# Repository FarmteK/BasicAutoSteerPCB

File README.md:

# BasicAutoSteerPCB

Repository of Eagle schematic and board. Parts list spreadsheet that can be imported into DigiKey's BOM and Cart interface. 

The Eagle files are in v7. Gerber and Drill files made by version 9.1.3

Board is roughly 100mm x 127mm or 4x5 inches.

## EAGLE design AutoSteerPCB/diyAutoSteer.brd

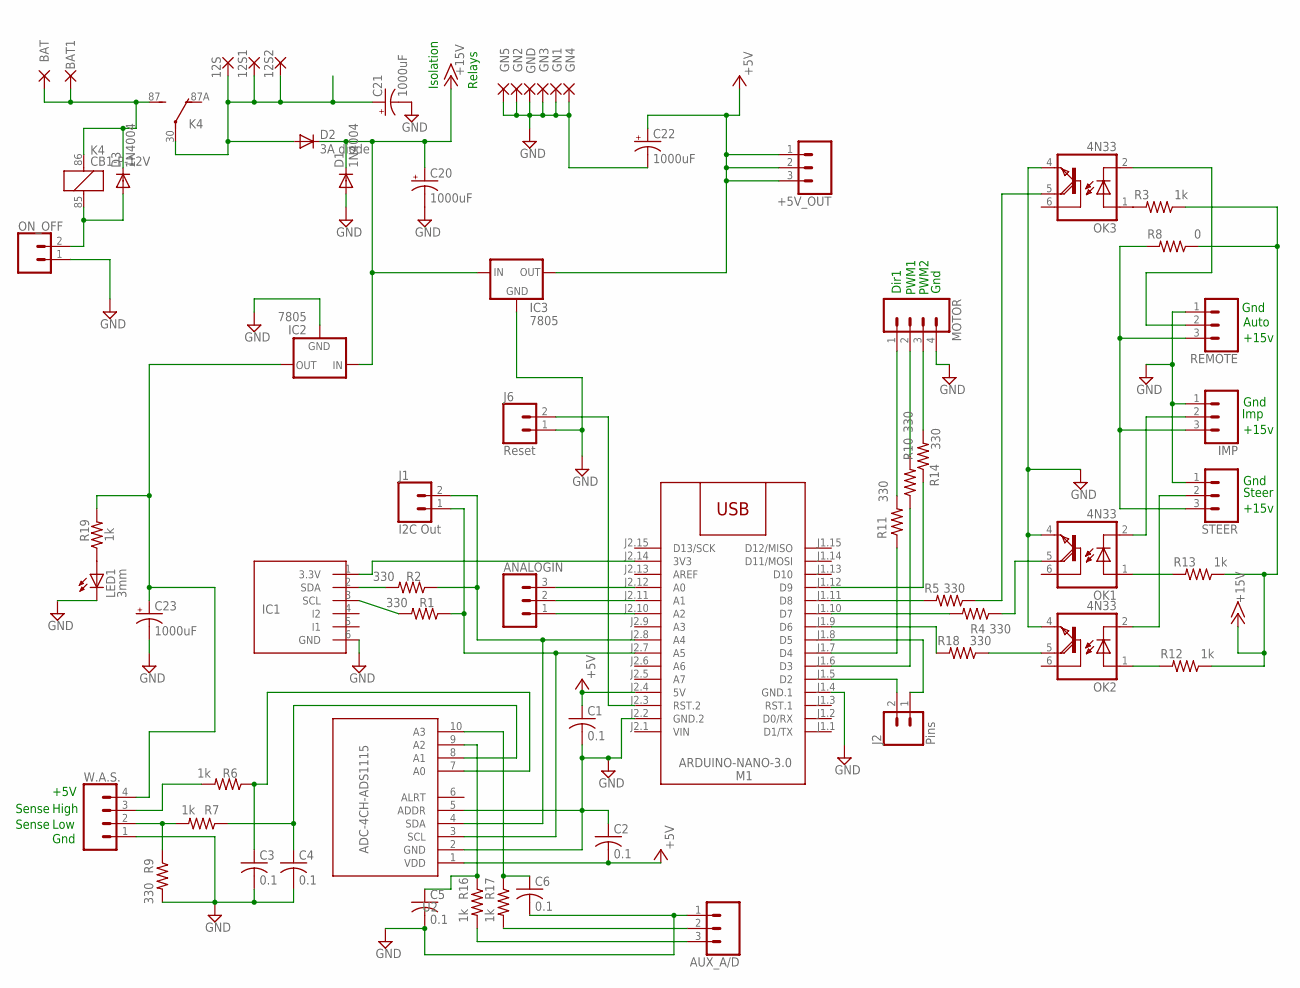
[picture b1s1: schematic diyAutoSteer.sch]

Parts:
12S, 12S1, 12S2: WIREPAD3,81/1,1; 3,81/1,1
+5V_OUT: CONN_03LONGPADS; 1X03_LONGPADS
ANALOGIN: CONN_03LONGPADS; 1X03_LONGPADS
AUX_A/D: CONN_03LONGPADS; 1X03_LONGPADS
BAT, BAT1: WIREPAD3,81/1,1; 3,81/1,1
C1, C2, C3, C4, C5, C6: 0.1; C025-025X050
C20, C21, C22, C23: 1000uF; E5-10,5
D1, D3: 1N4004; DO41-10
D2: 3A diode; DO27-15
GN1, GN2, GN3, GN4, GN5: WIREPAD3,81/1,1; 3,81/1,1
GND: WIREPAD3,81/1,1; 3,81/1,1
IC1: MMA8452Q; BREAKOUT_6PIN
IC2, IC3: 7805; 78XXS
IMP: CONN_03LONGPADS; 1X03_LONGPADS
J1: I2C Out; 1X02_LONGPADS
J2: Pins; 1X02_LONGPADS
J6: Reset; 1X02_LONGPADS
K4: CB1-P-12V; CB1
LED1: 3mm; LED3MM
M1: ARDUINO-NANO-3.0
MOTOR: CONN_04LONGPADS; 1X04_LONGPADS
OK1, OK2, OK3: 4N33; DIL06
ON_OFF: CONN_02PTH3; 1X02_LONGPADS
R1, R2, R4, R5, R9, R10, R11, R14, R18: 330; 0309/12
R3, R6, R7, R12, R13, R16, R17, R19: 1k; 0309/12
R8: 0; 0309/12
REMOTE: CONN_03LONGPADS; 1X03_LONGPADS
STEER: CONN_03LONGPADS; 1X03_LONGPADS
U2: ADC-4CH-ADS1115
W.A.S.: CONN_04LONGPADS; 1X04_LONGPADS

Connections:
+5V: +5V_OUT.1, +5V_OUT.2, +5V_OUT.3, C1.1, C2.2, C22.+, IC3.OUT, M1.J2.4 (5V), U2.1 (VDD)
+15V: C20.+, D1.C, D2.C, IC2.IN, IC3.IN, R3.1, R8.1, R12.1, R13.1
BATT: BAT.1, BAT1.1, D3.C, K4.86 (1), K4.87 (S)
GND: AUX_A/D.1, C1.2, C2.1, C3.2, C4.2, C5.2, C6.2, C20.-, C21.-, C22.-, C23.-, D1.A, GN1.1, GN2.1, GN3.1, GN4.1, GN5.1, GND.1, IC1.6 (GND), IC2.GND, IC3.GND, IMP.1, J6.1, LED1.K (C), M1.J1.4 (GND.1), M1.J2.2 (GND.2), MOTOR.4, OK1.4 (E), OK2.4 (E), OK3.4 (E), ON_OFF.1, R9.2, REMOTE.1, STEER.1, U2.2 (GND), U2.5 (ADDR), W.A.S..1
unnamed: IC1.1 (3.3V), M1.J2.14 (3V3)
unnamed: R7.2, R9.1, W.A.S..2
unnamed: IMP.3, R8.2, REMOTE.3, STEER.3
unnamed: M1.J1.6 (D3), R10.1
unnamed: M1.J1.7 (D4), R11.1
unnamed: J2.2, M1.J1.5 (D2)
unnamed: J6.2, M1.J2.3 (RST.2)
unnamed: R6.2, W.A.S..3
unnamed: ANALOGIN.3, M1.J2.12 (A0)
unnamed: M1.J1.12 (D9), R14.1
unnamed: IC1.2 (SDA), R2.2
unnamed: IC1.3 (SCL), R1.2
unnamed: ANALOGIN.2, M1.J2.11 (A1)
unnamed: ANALOGIN.1, M1.J2.10 (A2)
unnamed: LED1.A, R19.1
unnamed: MOTOR.2, R10.2
unnamed: J2.1, M1.J1.8 (D5)
unnamed: MOTOR.1, R11.2
unnamed: C3.1, R6.1, U2.7 (A0)
unnamed: MOTOR.3, R14.2
unnamed: OK2.2 (C), STEER.2
unnamed: M1.J1.11 (D8), R5.2
unnamed: D3.A, K4.85 (2), ON_OFF.2
unnamed: OK2.1 (A), R12.2
unnamed: OK3.1 (A), R3.2
unnamed: M1.J1.10 (D7), R4.2
unnamed: OK3.2 (C), REMOTE.2
unnamed: IMP.2, OK1.2 (C)
unnamed: M1.J1.9 (D6), R18.2
unnamed: OK1.1 (A), R13.2
unnamed: OK3.5 (COL), R5.1
unnamed: C6.1, R17.1, U2.10 (A3)
unnamed: C5.1, R16.1, U2.9 (A2)
unnamed: OK1.5 (COL), R4.1
unnamed: AUX_A/D.2, R17.2
unnamed: OK2.5 (COL), R18.1
unnamed: C4.1, R7.1, U2.8 (A1)
unnamed: AUX_A/D.3, R16.2
SCL: J1.1, M1.J2.7 (A5), R1.1, U2.3 (SCL)
SDA: J1.2, M1.J2.8 (A4), R2.1, U2.4 (SDA)
SW_RAW: 12S.1, 12S1.1, 12S2.1, C21.+, D2.A, K4.30
V+WAS: C23.+, IC2.OUT, R19.2, W.A.S..4
VIN: M1.J2.1 (VIN)

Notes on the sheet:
Gnd
Low
High
+5V
PWM1
PWM2
Dir1
Steer
Imp
Sense
Auto
Isolation
Relays
+15v

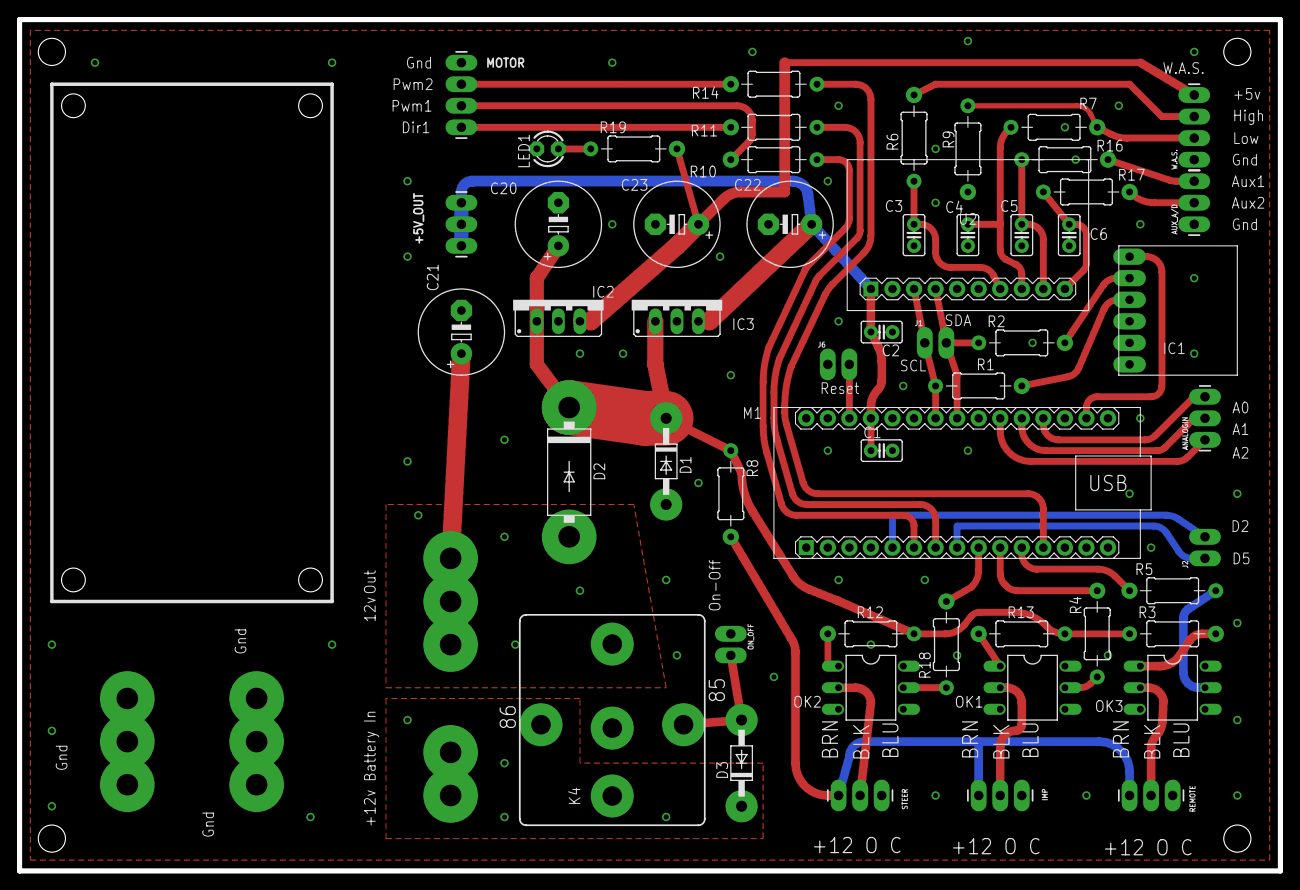
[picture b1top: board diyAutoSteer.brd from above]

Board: 2 copper layers, 148.6 x 100.3 mm, 64 parts (0 on the bottom side), 46 nets.

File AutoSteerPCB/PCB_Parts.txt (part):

Partlist exported from C:/Users/Grizs/Documents/eagle7/diyAutoSteer/diyAutoSteer.sch at 2019-03-16 10:13 PM

Part    Value            Device             Package          Description                                                       
12S     WIREPAD3,81/1,1  WIREPAD3,81/1,1    3,81/1,1         Wire PAD connect wire on PCB                                      
12S1    WIREPAD3,81/1,1  WIREPAD3,81/1,1    3,81/1,1         Wire PAD connect wire on PCB                                      
12S2    WIREPAD3,81/1,1  WIREPAD3,81/1,1    3,81/1,1         Wire PAD connect wire on PCB                                      
12S5    WIREPAD3,81/1,1  WIREPAD3,81/1,1    3,81/1,1         Wire PAD connect wire on PCB                                      
A1      A2               CONN_02PTH3        1X02_LONGPADS    Multi connection point. Often used as Generic Header-pin footprint
AUX_A/D                  CONN_03LONGPADS    1X03_LONGPADS    Multi connection point. Often used as Generic Header-pin footprint
BAT     WIREPAD3,81/1,1  WIREPAD3,81/1,1    3,81/1,1         Wire PAD connect wire on PCB                                      
BAT1    WIREPAD3,81/1,1  WIREPAD3,81/1,1    3,81/1,1         Wire PAD connect wire on PCB                                      
C1      0.1              C-US025-025X050    C025-025X050     CAPACITOR, American symbol                                        
C2      0.1              C-US025-025X050    C025-025X050     CAPACITOR, American symbol                                        
C3      0.1              C-US025-025X050    C025-025X050     CAPACITOR, American symbol                                        
C4      0.1              C-US025-025X050    C025-025X050     CAPACITOR, American symbol                                        
C5      0.1              C-US025-025X050    C025-025X050     CAPACITOR, American symbol                                        
C6      0.1              C-US025-025X050    C025-025X050     CAPACITOR, American symbol                                        
C20     1000uF           CPOL-USE5-10.5     E5-10,5          POLARIZED CAPACITOR, American symbol                              
C21     1000uF           CPOL-USE5-10.5     E5-10,5          POLARIZED CAPACITOR, American symbol                              
C22     1000uF           CPOL-USE5-10.5     E5-10,5          POLARIZED CAPACITOR, American symbol                              
C23     1000uF           CPOL-USE5-10.5     E5-10,5          POLARIZED CAPACITOR, American symbol                              
D1      1N4004           1N4004             DO41-10          DIODE                                                             
D2      1N4004           1N4004             DO41-10          DIODE                                                             
D3      1N4004           1N4004             DO41-10          DIODE                                                             
D5                       CONN_01PTH_LONGPAD 1X01_LONGPAD     Single connection point. Often used as Generic Header-pin footprin
GN1     WIREPAD3,81/1,1  WIREPAD3,81/1,1    3,81/1,1         Wire PAD connect wire on PCB                                      
GN2     WIREPAD3,81/1,1  WIREPAD3,81/1,1    3,81/1,1         Wire PAD connect wire on PCB                                      
GN3     WIREPAD3,81/1,1  WIREPAD3,81/1,1    3,81/1,1         Wire PAD connect wire on PCB                                      
GN4     WIREPAD3,81/1,1  WIREPAD3,81/1,1    3,81/1,1         Wire PAD connect wire on PCB                                      
GN5     WIREPAD3,81/1,1  WIREPAD3,81/1,1    3,81/1,1         Wire PAD connect wire on PCB                                      
GND     WIREPAD3,81/1,1  WIREPAD3,81/1,1    3,81/1,1         Wire PAD connect wire on PCB                                      
IC1                      MMA8452Q           BREAKOUT_6PIN                                                                      
IC2     7805             78XXS              78XXS            VOLTAGE REGULATOR                                                 
IC3     7805             78XXS              78XXS            VOLTAGE REGULATOR                                                 
IMP                      CONN_03LONGPADS    1X03_LONGPADS    Multi connection point. Often used as Generic Header-pin footprint
INT0                     CONN_01PTH_LONGPAD 1X01_LONGPAD     Single connection point. Often used as Generic Header-pin footprin
J1      I2C Out          CONN_02PTH3        1X02_LONGPADS    Multi connection point. Often used as Generic Header-pin footprint
J6      Reset            CONN_02PTH3        1X02_LONGPADS    Multi connection point. Often used as Generic Header-pin footprint
K4      CB1-P-12V        CB1-P-12V          CB1              HIGH POWER AUTOMOTIVE RELAY Form C NAiS                           
LED1    3mm              LED3MM             LED3MM           LED                                                               
M1      ARDUINO-NANO-3.0 ARDUINO-NANO-3.0   ARDUINO-NANO-3.0 Arduino Nano 3.0 and compatible devices                           
MOTOR                    CONN_04LONGPADS    1X04_LONGPADS    Multi connection point. Often used as Generic Header-pin footprint
OK1     4N33             4N33               DIL06            MOTOROLA OPTO COUPLER                                             
OK2     4N33             4N33               DIL06            MOTOROLA OPTO COUPLER                                             
OK3     4N33             4N33               DIL06            MOTOROLA OPTO COUPLER                                             
ON_OFF                   CONN_02PTH3        1X02_LONGPADS    Multi connection point. Often used as Generic Header-pin footprint
R1      330              R-US_0309/12       0309/12          RESISTOR, American symbol                                         
R2      330              R-US_0309/12       0309/12          RESISTOR, American symbol                                         
R3      1k               R-US_0309/12       0309/12          RESISTOR, American symbol                                         
R4      330              R-US_0309/12       0309/12          RESISTOR, American symbol                                         
R5      330              R-US_0309/12       0309/12          RESISTOR, American symbol                                         
R6      1k               R-US_0309/12       0309/12          RESISTOR, American symbol                                         
R7      1k               R-US_0309/12       0309/12          RESISTOR, American symbol                                         
R8      47               R-US_0309/12       0309/12          RESISTOR, American symbol                                         
R9      330              R-US_0309/12       0309/12          RESISTOR, American symbol                                         
R10     330              R-US_0309/12       0309/12          RESISTOR, American symbol                                         
R11     330              R-US_0309/12       0309/12          RESISTOR, American symbol                                         
R12     1k               R-US_0309/12       0309/12          RESISTOR, American symbol                                         
R13     1k               R-US_0309/12       0309/12          RESISTOR, American symbol                                         
R14     330              R-US_0309/12       0309/12          RESISTOR, American symbol                                         
R16     1k               R-US_0309/12       0309/12          RESISTOR, American symbol                                         
R17     1k               R-US_0309/12       0309/12          RESISTOR, American symbol                                         
R18     330              R-US_0309/12       0309/12          RESISTOR, American symbol                                         
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
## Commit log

2019-03-17 Basic AutoSteer PCB
    Board and parts
2019-03-19 Create SectionRelayInput.zip
    The section pcb
2019-03-19 Fix Direcory Names
    Separate into 2 directories
2019-03-20 Added RelayPCB Parts list
    Parts list add
2019-04-01 Added ADS1115 to parts
    Missed part, change R8 to zero ohms
2019-04-18 Added Arduino code
    INO code added
2019-04-29 v2 PCB
    v2 PCB
2019-05-01 Code fixed
    Arduino code fixed with Setup for wrong directions etc
2019-06-20 Version 2
    Version 2 of PCB
2019-06-25 Create PartsList.txt
    Just components

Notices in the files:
parts and their libraries:
SparkFun-Connectors: Licensing: Creative Commons ShareAlike 4.0 International - https://creativecommons.org/licenses/by-sa/4.0
diy-modules: Released under the Creative Commons Attribution 4.0 International License: http://creativecommons.org/licenses/by/4.0
